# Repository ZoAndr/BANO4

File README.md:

# BANO4
OnBoard Aviation Navigation Lights

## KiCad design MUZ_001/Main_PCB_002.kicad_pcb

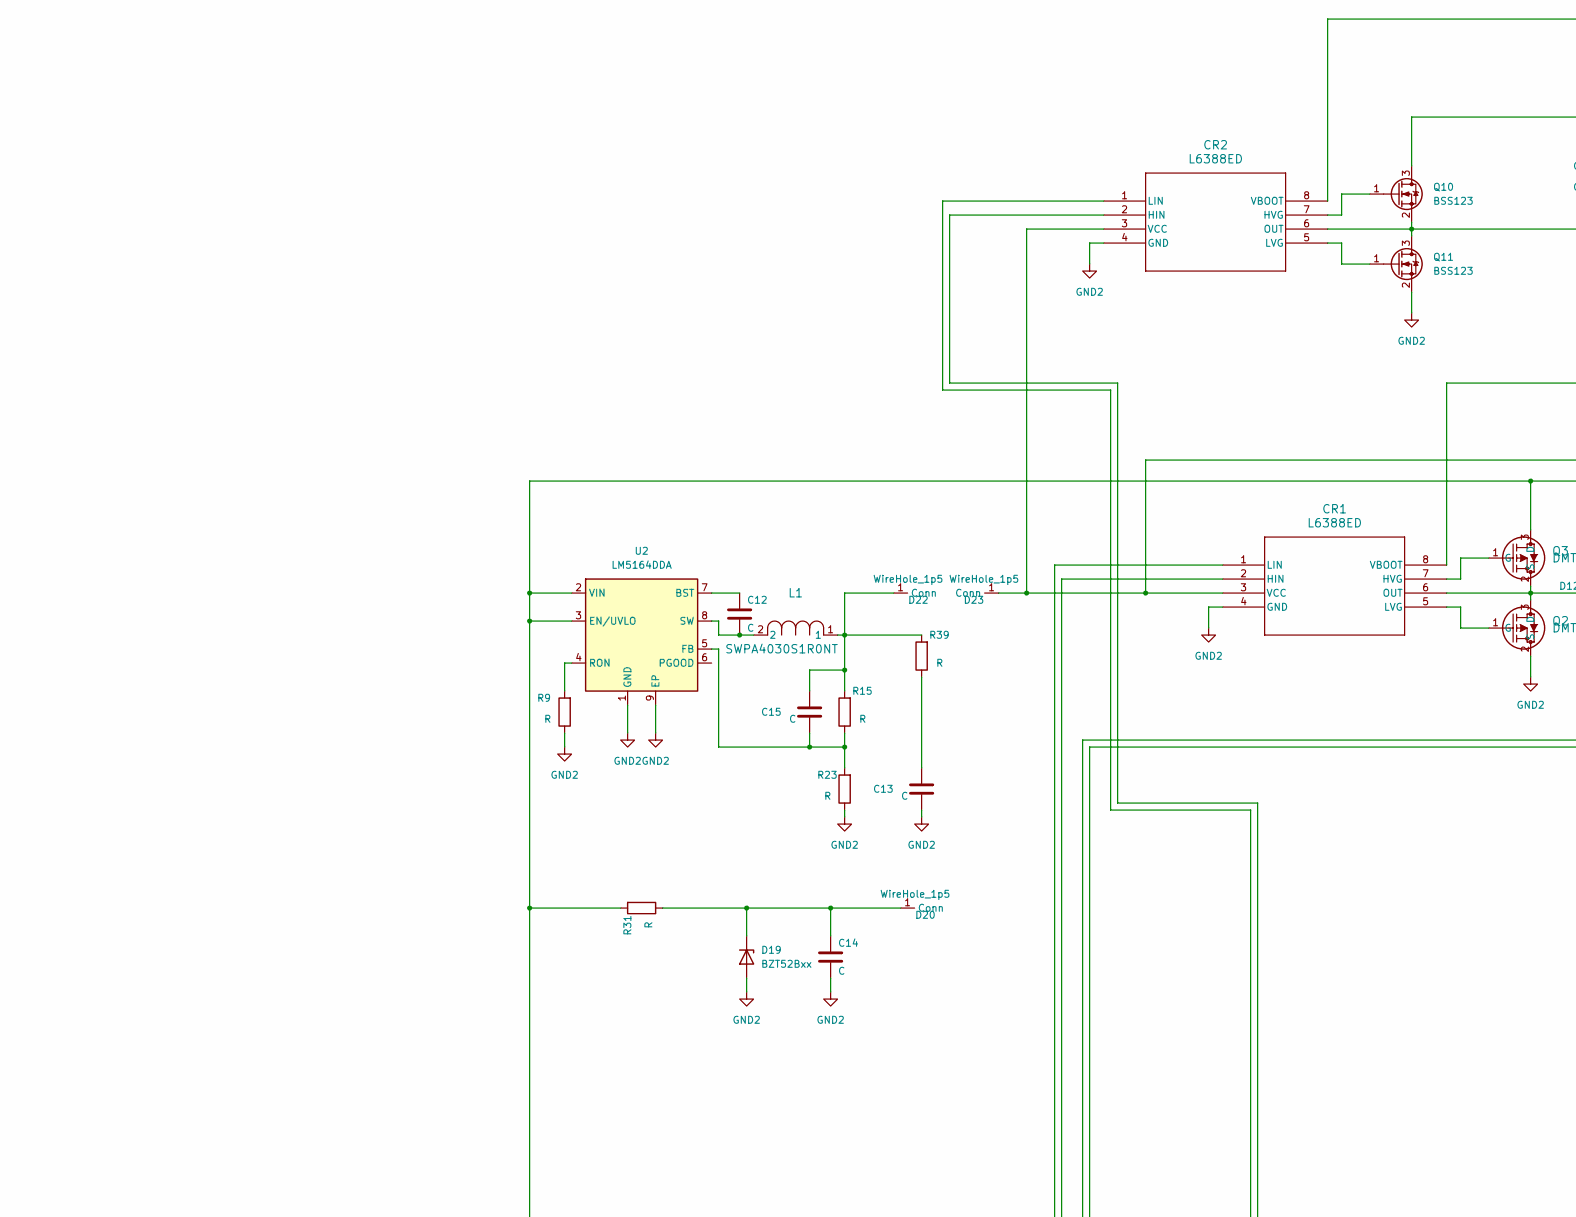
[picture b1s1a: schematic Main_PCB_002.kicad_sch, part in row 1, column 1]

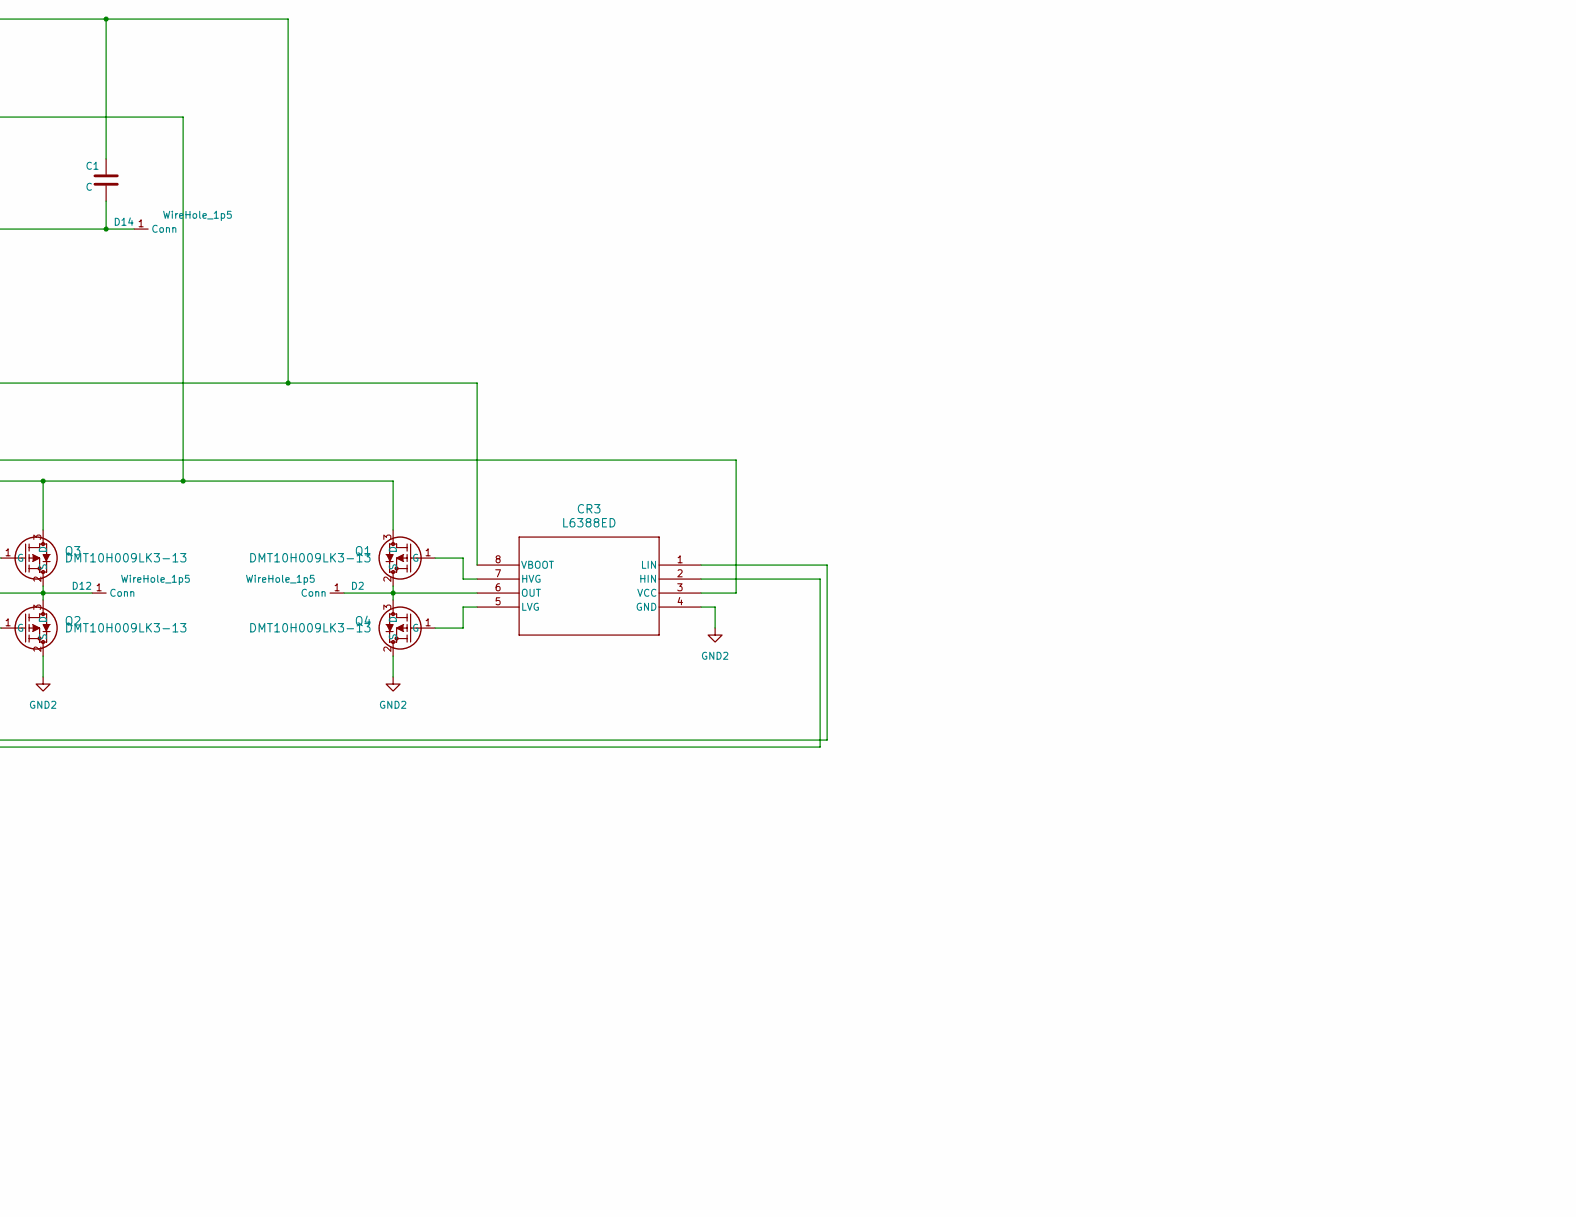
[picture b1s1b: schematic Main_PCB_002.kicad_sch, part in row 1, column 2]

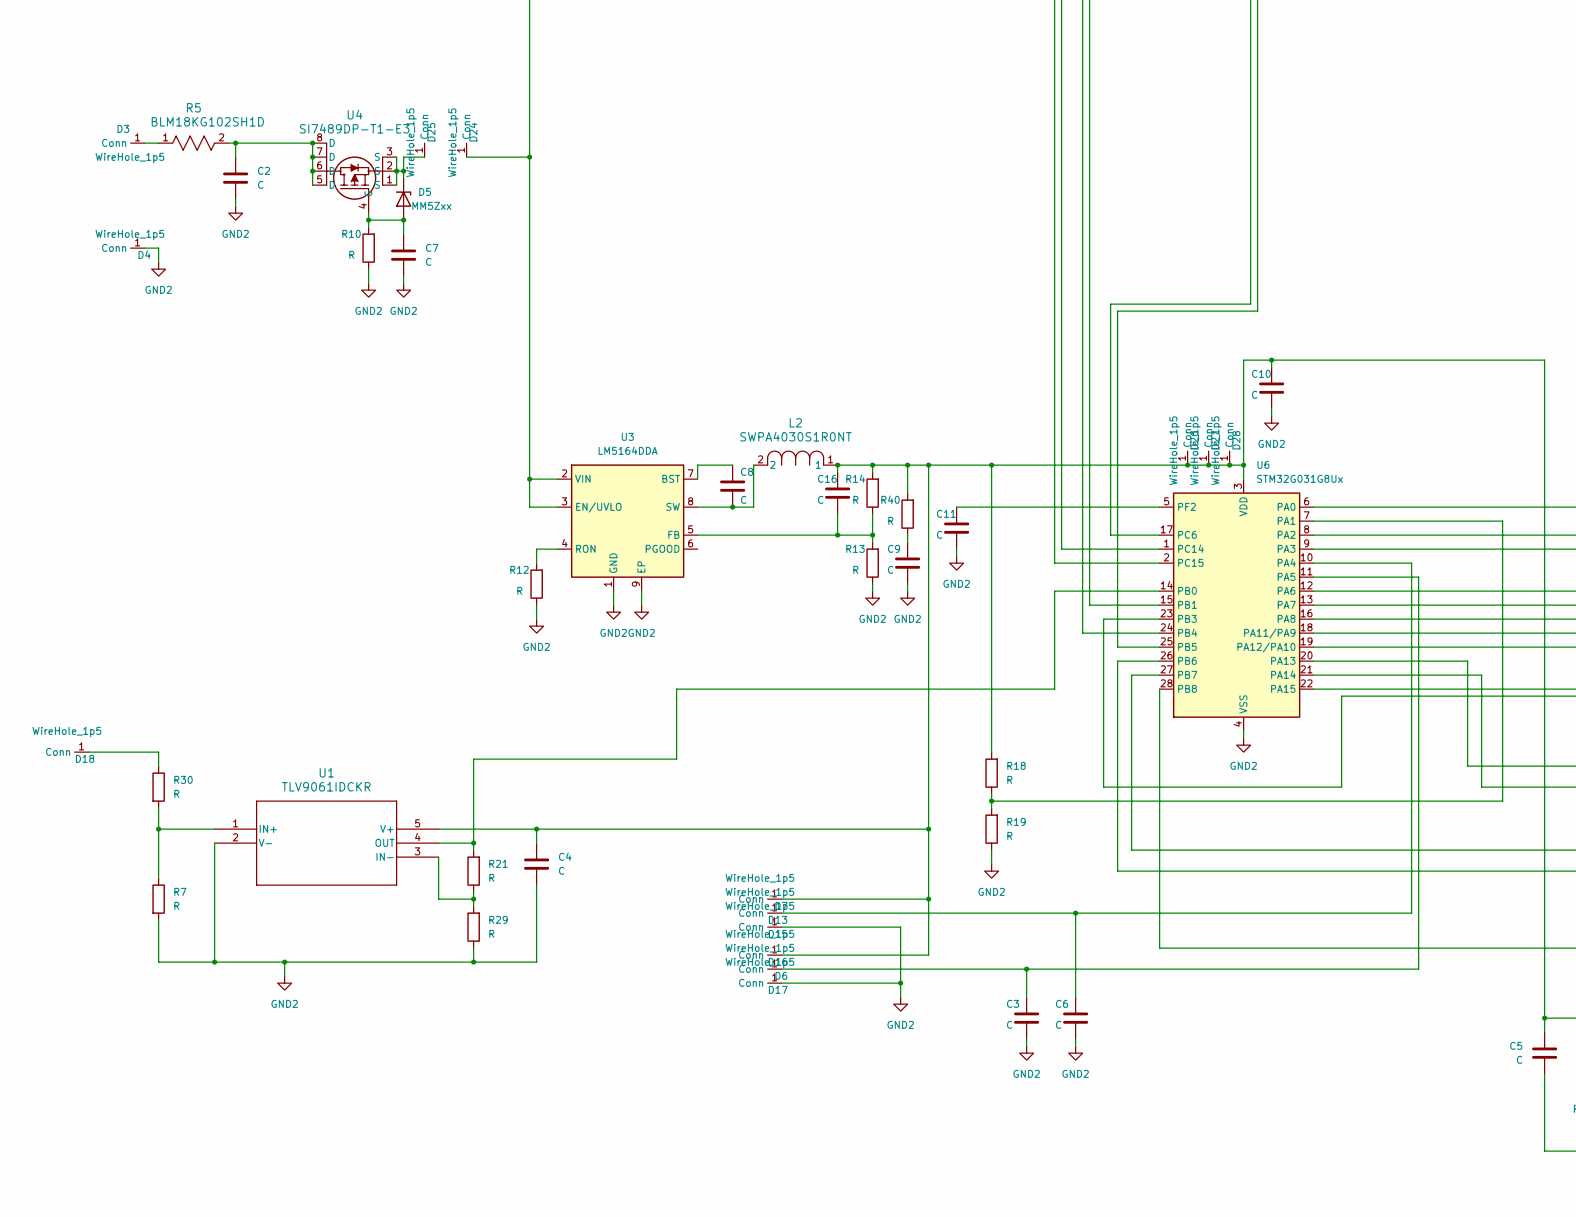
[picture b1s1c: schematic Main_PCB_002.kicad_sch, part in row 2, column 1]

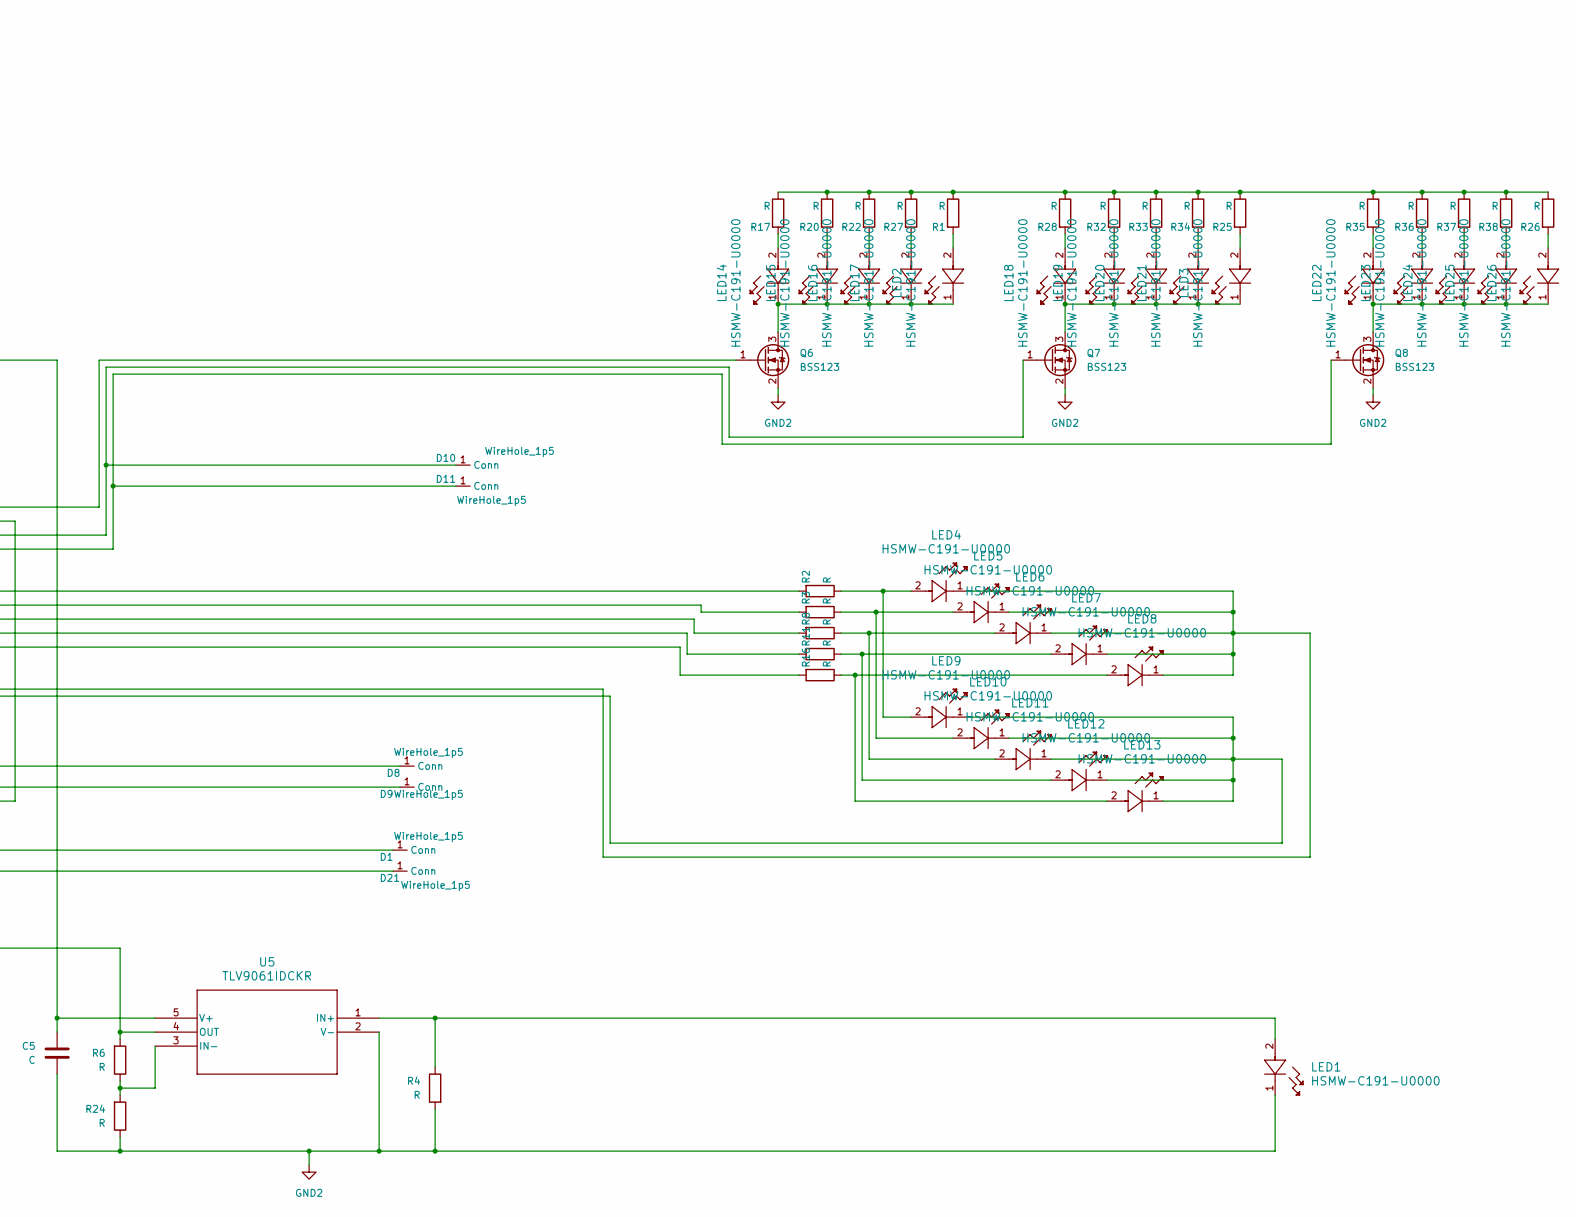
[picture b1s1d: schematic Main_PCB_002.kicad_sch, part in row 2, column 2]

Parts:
C1, C3, C6, C9, C13: C; C_0805_2012Metric
C2: C; C_0805_2012Metric_Pad1.18x1.45mm_HandSolder
C4, C5, C7, C16: C; C_0402_1005Metric_Pad0.74x0.62mm_HandSolder
C8, C10, C11, C12, C14: C; C_0603_1608Metric_Pad1.08x0.95mm_HandSolder
C15: C; C_0402_1005Metric
CR1, CR2, CR3: L6388ED; SO-8_STM
D1, D2, D3, D4, D6, D7, D8, D9, D10, D11, D12, D13, D14, D15, D16, D17, D18, D20, D21, D22, D23, D24, D25, D26, D27, D28: WireHole_1p5; WireHole_1p2
D5: MM5Zxx; D_SOD-523
D19: BZT52Bxx; D_SOD-123F
L1, L2: SWPA4030S1R0NT; IND_VLS252012_TDK
LED1, LED2, LED3, LED4, LED5, LED6, LED7, LED8, LED9, LED10, LED11, LED12, LED13, LED14, LED15, LED16, LED17, LED18, LED19, LED20, LED21, LED22, LED23, LED24, LED25, LED26: HSMW-C191-U0000; LED_91-U0000
Q1, Q2, Q3, Q4: DMT10H009LK3-13; QPMOS1G2S3D_TO252_DIO
Q6, Q7, Q8, Q10, Q11: BSS123; SOT-23
R1, R2, R3, R4, R6, R7, R8, R9, R10, R11, R12, R13, R14, R15, R16, R17, R18, R19, R20, R21, R22, R23, R24, R25, R26, R27, R28, R29, R30, R31, R32, R33, R34, R35, R36, R37, R38, R39, R40: R; R_0402_1005Metric_Pad0.72x0.64mm_HandSolder
R5: BLM18KG102SH1D; RES_0603_1P6XP8_MUR
U1, U5: TLV9061IDCKR; DCK5_TEX
U2, U3: LM5164DDA; HSOP-8-1EP_3.9x4.9mm_P1.27mm_EP2.41x3.1mm_ThermalVias
U4: SI7489DP-T1-E3; POWERPAK_SO-8_SINGLE_VIS
U6: STM32G031G8Ux; QFN-28_4x4mm_P0.5mm

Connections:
GND2: C2.2, C3.2, C4.2, C5.2, C6.2, C7.2, C9.2, C10.2, C11.2, C13.2, C14.2, CR1.4 (GND), CR2.4 (GND), CR3.4 (GND), D4.1 (Conn), D15.1 (Conn), D17.1 (Conn), D19.2 (A), LED1.1, Q2.2 (S), Q4.2 (S), Q6.2 (S), Q7.2 (S), Q8.2 (S), Q11.2 (S), R4.2, R7.2, R9.1, R10.1, R12.1, R13.1, R19.1, R23.1, R24.1, R29.1, U1.2 (V-), U2.1 (GND), U2.9 (EP), U3.1 (GND), U3.9 (EP), U5.2 (V-), U6.4 (VSS)
unnamed: C2.1, R5.2, U4.5 (D), U4.6 (D), U4.7 (D), U4.8 (D)
unnamed: C9.1, R40.1
unnamed: C13.1, R39.1
unnamed: CR1.2 (HIN), U6.1 (PC14)
unnamed: CR1.7 (HVG), Q3.1 (G)
unnamed: CR1.1 (LIN), U6.2 (PC15)
unnamed: CR1.5 (LVG), Q2.1 (G)
unnamed: CR1.6 (OUT), D12.1 (Conn), Q2.3 (D), Q3.2 (S)
unnamed: C1.1, CR1.8 (VBOOT), CR2.8 (VBOOT), CR3.8 (VBOOT)
unnamed: CR1.3 (VCC), CR2.3 (VCC), CR3.3 (VCC), D23.1 (Conn)
unnamed: CR2.2 (HIN), U6.25 (PB5)
unnamed: CR2.7 (HVG), Q10.1 (G)
unnamed: CR2.1 (LIN), U6.17 (PC6)
unnamed: CR2.5 (LVG), Q11.1 (G)
unnamed: C1.2, CR2.6 (OUT), D14.1 (Conn), Q10.2 (S), Q11.3 (D)
unnamed: CR3.2 (HIN), U6.15 (PB1)
unnamed: CR3.7 (HVG), Q1.1 (G)
unnamed: CR3.1 (LIN), U6.24 (PB4)
unnamed: CR3.5 (LVG), Q4.1 (G)
unnamed: CR3.6 (OUT), D2.1 (Conn), Q1.2 (S), Q4.3 (D)
unnamed: D1.1 (Conn), U6.27 (PB7)
unnamed: D3.1 (Conn), R5.1
unnamed: C7.1, D5.2 (A), R10.2, U4.4 (G)
unnamed: C3.1, D6.1 (Conn), U6.11 (PA5)
unnamed: D8.1 (Conn), U6.20 (PA13)
unnamed: D9.1 (Conn), U6.21 (PA14)
unnamed: D10.1 (Conn), Q7.1 (G), U6.8 (PA2)
unnamed: D11.1 (Conn), Q8.1 (G), U6.9 (PA3)
unnamed: C6.1, D13.1 (Conn), U6.10 (PA4)
unnamed: C4.1, C5.1, C10.1, C16.1, D7.1 (Conn), D16.1 (Conn), D26.1 (Conn), D27.1 (Conn), D28.1 (Conn), L2.1, R14.2, R18.2, R40.2, U1.5 (V+), U5.5 (V+), U6.3 (VDD)
unnamed: D18.1 (Conn), R30.1
unnamed: C14.1, D19.1 (K), D20.1 (Conn), R31.1
unnamed: D21.1 (Conn), U6.26 (PB6)
unnamed: C15.1, D22.1 (Conn), L1.1, R15.2, R39.2
unnamed: D24.1 (Conn), Q1.3 (D), Q3.3 (D), Q10.3 (D), R31.2, U2.2 (VIN), U2.3 (EN/UVLO), U3.2 (VIN), U3.3 (EN/UVLO)
unnamed: D5.1 (K), D25.1 (Conn), U4.1 (S), U4.2 (S), U4.3 (S)
unnamed: LED2.2, R1.2
unnamed: LED3.2, R25.2
unnamed: LED4.2, LED9.2, R2.1
unnamed: LED5.2, LED10.2, R3.1
unnamed: LED6.2, LED11.2, R8.1
unnamed: LED7.2, LED12.2, R11.1
unnamed: LED8.2, LED13.2, R16.1
unnamed: LED14.2, R17.2
unnamed: LED15.2, R20.2
unnamed: LED16.2, R22.2
unnamed: LED17.2, R27.2
unnamed: LED18.2, R28.2
unnamed: LED19.2, R32.2
unnamed: LED20.2, R33.2
unnamed: LED21.2, R34.2
unnamed: LED22.2, R35.2
unnamed: LED23.2, R36.2
unnamed: LED24.2, R37.2
unnamed: LED25.2, R38.2
unnamed: LED26.2, R26.2
unnamed: LED2.1, LED14.1, LED15.1, LED16.1, LED17.1, Q6.3 (D)
unnamed: Q6.1 (G), U6.6 (PA0)
unnamed: LED3.1, LED18.1, LED19.1, LED20.1, LED21.1, Q7.3 (D)
unnamed: LED22.1, LED23.1, LED24.1, LED25.1, LED26.1, Q8.3 (D)
unnamed: R1.1, R17.1, R20.1, R22.1, R25.1, R26.1, R27.1, R28.1, R32.1, R33.1, R34.1, R35.1, R36.1, R37.1, R38.1
unnamed: R7.1, R30.2, U1.1 (IN+)
unnamed: R21.1, R29.2, U1.3 (IN-)
unnamed: R21.2, U1.4 (OUT), U6.14 (PB0)
unnamed: C12.1, U2.7 (BST)
unnamed: C15.2, R15.1, R23.2, U2.5 (FB)
unnamed: R9.2, U2.4 (RON)
unnamed: C12.2, L1.2, U2.8 (SW)
unnamed: C8.1, U3.7 (BST)
unnamed: C16.2, R13.2, R14.1, U3.5 (FB)
unnamed: R12.2, U3.4 (RON)
unnamed: C8.2, L2.2, U3.8 (SW)
unnamed: LED1.2, R4.1, U5.1 (IN+)
unnamed: R6.1, R24.2, U5.3 (IN-)
unnamed: R6.2, U5.4 (OUT), U6.28 (PB8)
unnamed: R18.1, R19.2, U6.7 (PA1)
unnamed: R2.2, U6.12 (PA6)
unnamed: R3.2, U6.13 (PA7)
unnamed: R8.2, U6.16 (PA8)
unnamed: R11.2, U6.18 (PA11/PA9)
unnamed: R16.2, U6.19 (PA12/PA10)
unnamed: LED4.1, LED5.1, LED6.1, LED7.1, LED8.1, U6.22 (PA15)
unnamed: LED9.1, LED10.1, LED11.1, LED12.1, LED13.1, U6.23 (PB3)
unnamed: C11.1, U6.5 (PF2)

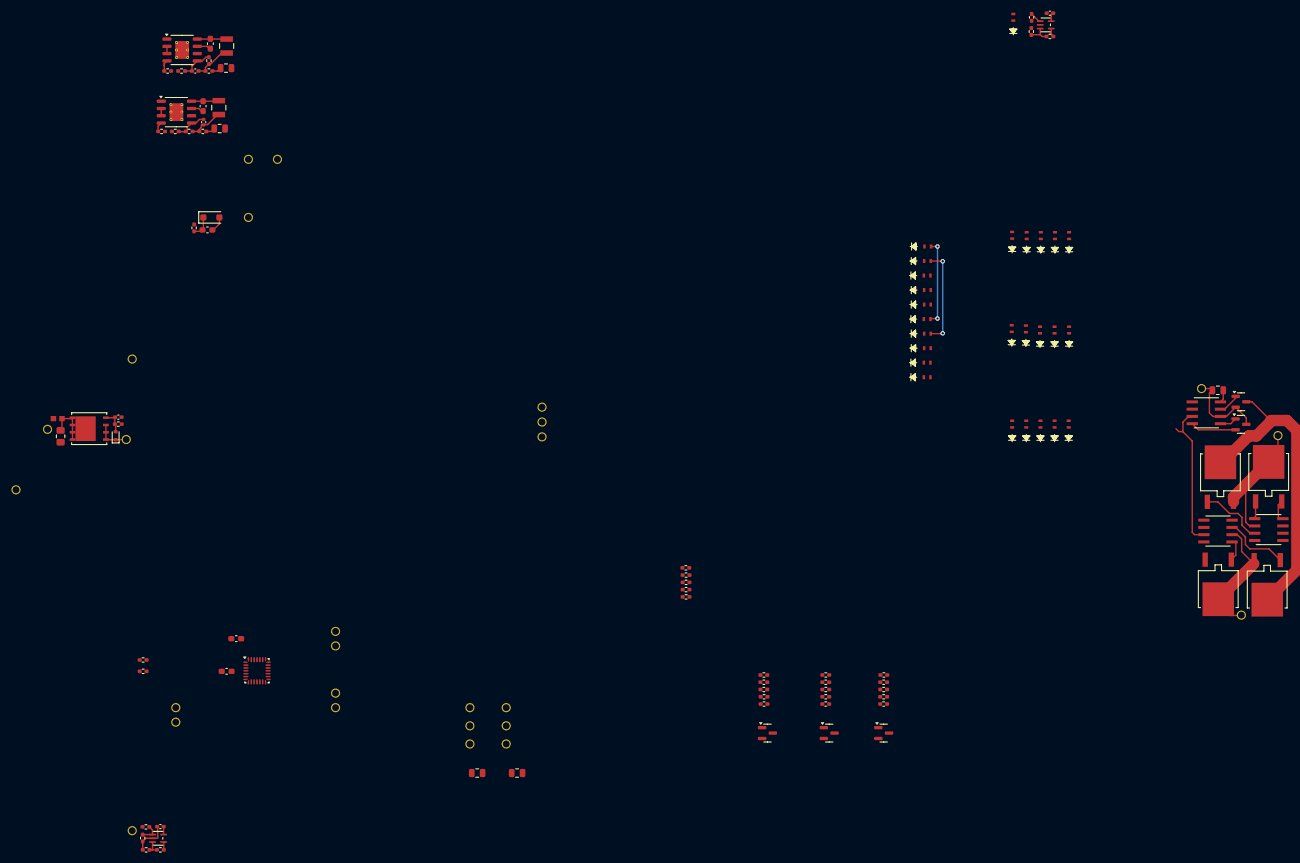
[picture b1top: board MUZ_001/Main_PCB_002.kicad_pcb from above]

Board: 2 copper layers, 130 parts (0 on the bottom side), 85 nets.

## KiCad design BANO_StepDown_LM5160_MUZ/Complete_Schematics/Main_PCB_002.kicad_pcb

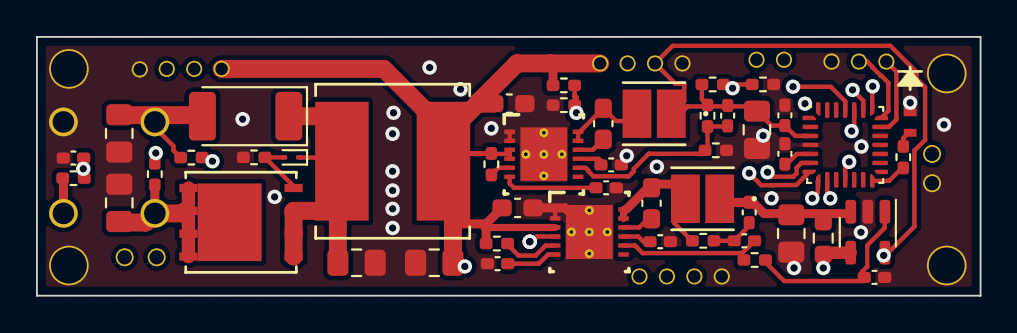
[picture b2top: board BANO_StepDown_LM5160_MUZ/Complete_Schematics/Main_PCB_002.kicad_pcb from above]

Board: 4 copper layers, 52.4 x 14.4 mm, 77 parts (0 on the bottom side), 39 nets.

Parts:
C1, C2, C4, C5, C15, C19: C; C_0805_2012Metric_Pad1.18x1.45mm_HandSolder
C3, C6, C7, C9, C11, C13, C16, C17, C18, C20, C21: C; C_0402_1005Metric_Pad0.74x0.62mm_HandSolder
C8, C10, C12, C14: C; C_0603_1608Metric_Pad1.08x0.95mm_HandSolder
D1, D2, D3, D19: WireHole_1p5; WireHole_1p2
D4: 1N5711UR; D_MELF
D5: MM5Zxx; D_SOD-923
D6, D7, D8, D9, D10, D11, D12, D13, D14, D20, D21, D22, D23, D24, D25, D26, D27: WireHole_1p5; WireHole_0p7
D15, D16, D17, D18: WireHole_1p5; WireHole_0p8
D28, D29, D30, D31: WireHole_1p5; WireHole_2p0
L1: SWPA8040S220MT; IND_SWPA8040S_SNL
L2, L3: SWPA3015S4R7MT; IND_SWPA3015S_SNL
LED1: HSMW-C191-U0000; LED_91-U0000
R1, R2, R3, R4, R5, R6, R7, R8, R9, R10, R11, R12, R13, R14, R15: R; R_0402_1005Metric_Pad0.72x0.64mm_HandSolder
R16: R; R_0603_1608Metric_Pad0.98x0.95mm_HandSolder
U1: SI7489DP-T1-E3; POWERPAK_SO-8_SINGLE_VIS
U2: STM32G031G8Ux; QFN-28_4x4mm_P0.5mm
U3, U4: LM5160ADNTR; DNT0012B
U5: INA193; SOT-23-5

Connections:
GND2: C1.2, C2.2, C3.2, C4.2, C5.2, C6.2, C7.2, C8.2, C9.2, C10.2, C11.2, C13.2, C15.2, C16.2, C19.2, C20.2, D10.1 (Conn), D14.1 (Conn), D18.1 (Conn), D19.1 (Conn), D20.1 (Conn), D21.1 (Conn), D28.1 (Conn), D29.1 (Conn), D30.1 (Conn), D31.1 (Conn), LED1.1, R4.1, R6.1, R8.1, R15.1, U2.4 (VSS), U3.1 (AGND), U3.2 (PGND), U3.13 (PAD), U3.V, U4.1 (AGND), U4.2 (PGND), U4.13 (PAD), U4.V, U5.2 (GND)
unnamed: C12.2, L2.2, R12.2, U3.11 (SW), U3.12 (SW)
unnamed: C14.2, L3.2, U4.11 (SW), U4.12 (SW)
unnamed: C17.2, C18.1, R12.1
unnamed: D1.1 (Conn), R3.2
unnamed: C1.1, D2.1 (Conn), D4.2 (A), R2.1
unnamed: C2.1, D3.1 (Conn), R1.1, U1.5 (D), U1.6 (D), U1.7 (D), U1.8 (D)
unnamed: C4.1, D4.1 (K), D5.1 (K), L1.2, U1.1 (S), U1.2 (S), U1.3 (S)
unnamed: D5.2 (A), R4.2, U1.4 (G)
unnamed: D6.1 (Conn), U2.8 (PA2)
unnamed: D7.1 (Conn), U2.9 (PA3)
unnamed: D8.1 (Conn), U2.20 (PA13)
unnamed: D9.1 (Conn), U2.21 (PA14)
unnamed: C5.1, C8.1, C10.1, D11.1 (Conn), D26.1 (Conn), D27.1 (Conn), L1.1, R7.2, R10.2, R11.2, U3.3 (VIN), U4.3 (VIN), U4.4 (EN_UVLO)
unnamed: D12.1 (Conn), D24.1 (Conn), D25.1 (Conn), U2.22 (PA15)
unnamed: C7.1, C19.1, C20.1, C21.1, D13.1 (Conn), D22.1 (Conn), D23.1 (Conn), L3.1, R5.2, R14.2, U2.3 (VDD), U5.5 (V+)
unnamed: D15.1 (Conn), R16.1, U5.4 (-)
unnamed: D16.1 (Conn), D17.1 (Conn)
unnamed: LED1.2, R9.1
unnamed: R13.1, U5.1
unnamed: R7.1, R8.2, U2.6 (PA0)
unnamed: R5.1, R6.2, U2.7 (PA1)
unnamed: C3.1, R3.1, U2.11 (PA5)
unnamed: R9.2, U2.14 (PB0)
unnamed: U2.23 (PB3), U3.4 (EN_UVLO)
unnamed: R2.2, U2.24 (PB4)
unnamed: R1.2, U2.25 (PB5)
unnamed: C6.1, U2.5 (PF2)
unnamed: C12.1, U3.10 (BST)
unnamed: C18.2, R13.2, U3.8 (FB)
unnamed: R10.1, U3.5 (RON)
unnamed: C9.1, U3.6 (SS)
unnamed: C13.1, U3.9 (VCC)
unnamed: C14.1, U4.10 (BST)
unnamed: C21.2, R14.1, R15.2, U4.8 (FB)
unnamed: R11.1, U4.5 (RON)
unnamed: C11.1, U4.6 (SS)
unnamed: C16.1, U4.9 (VCC)
unnamed: C15.1, C17.1, L2.1, R16.2, U5.3 (+)

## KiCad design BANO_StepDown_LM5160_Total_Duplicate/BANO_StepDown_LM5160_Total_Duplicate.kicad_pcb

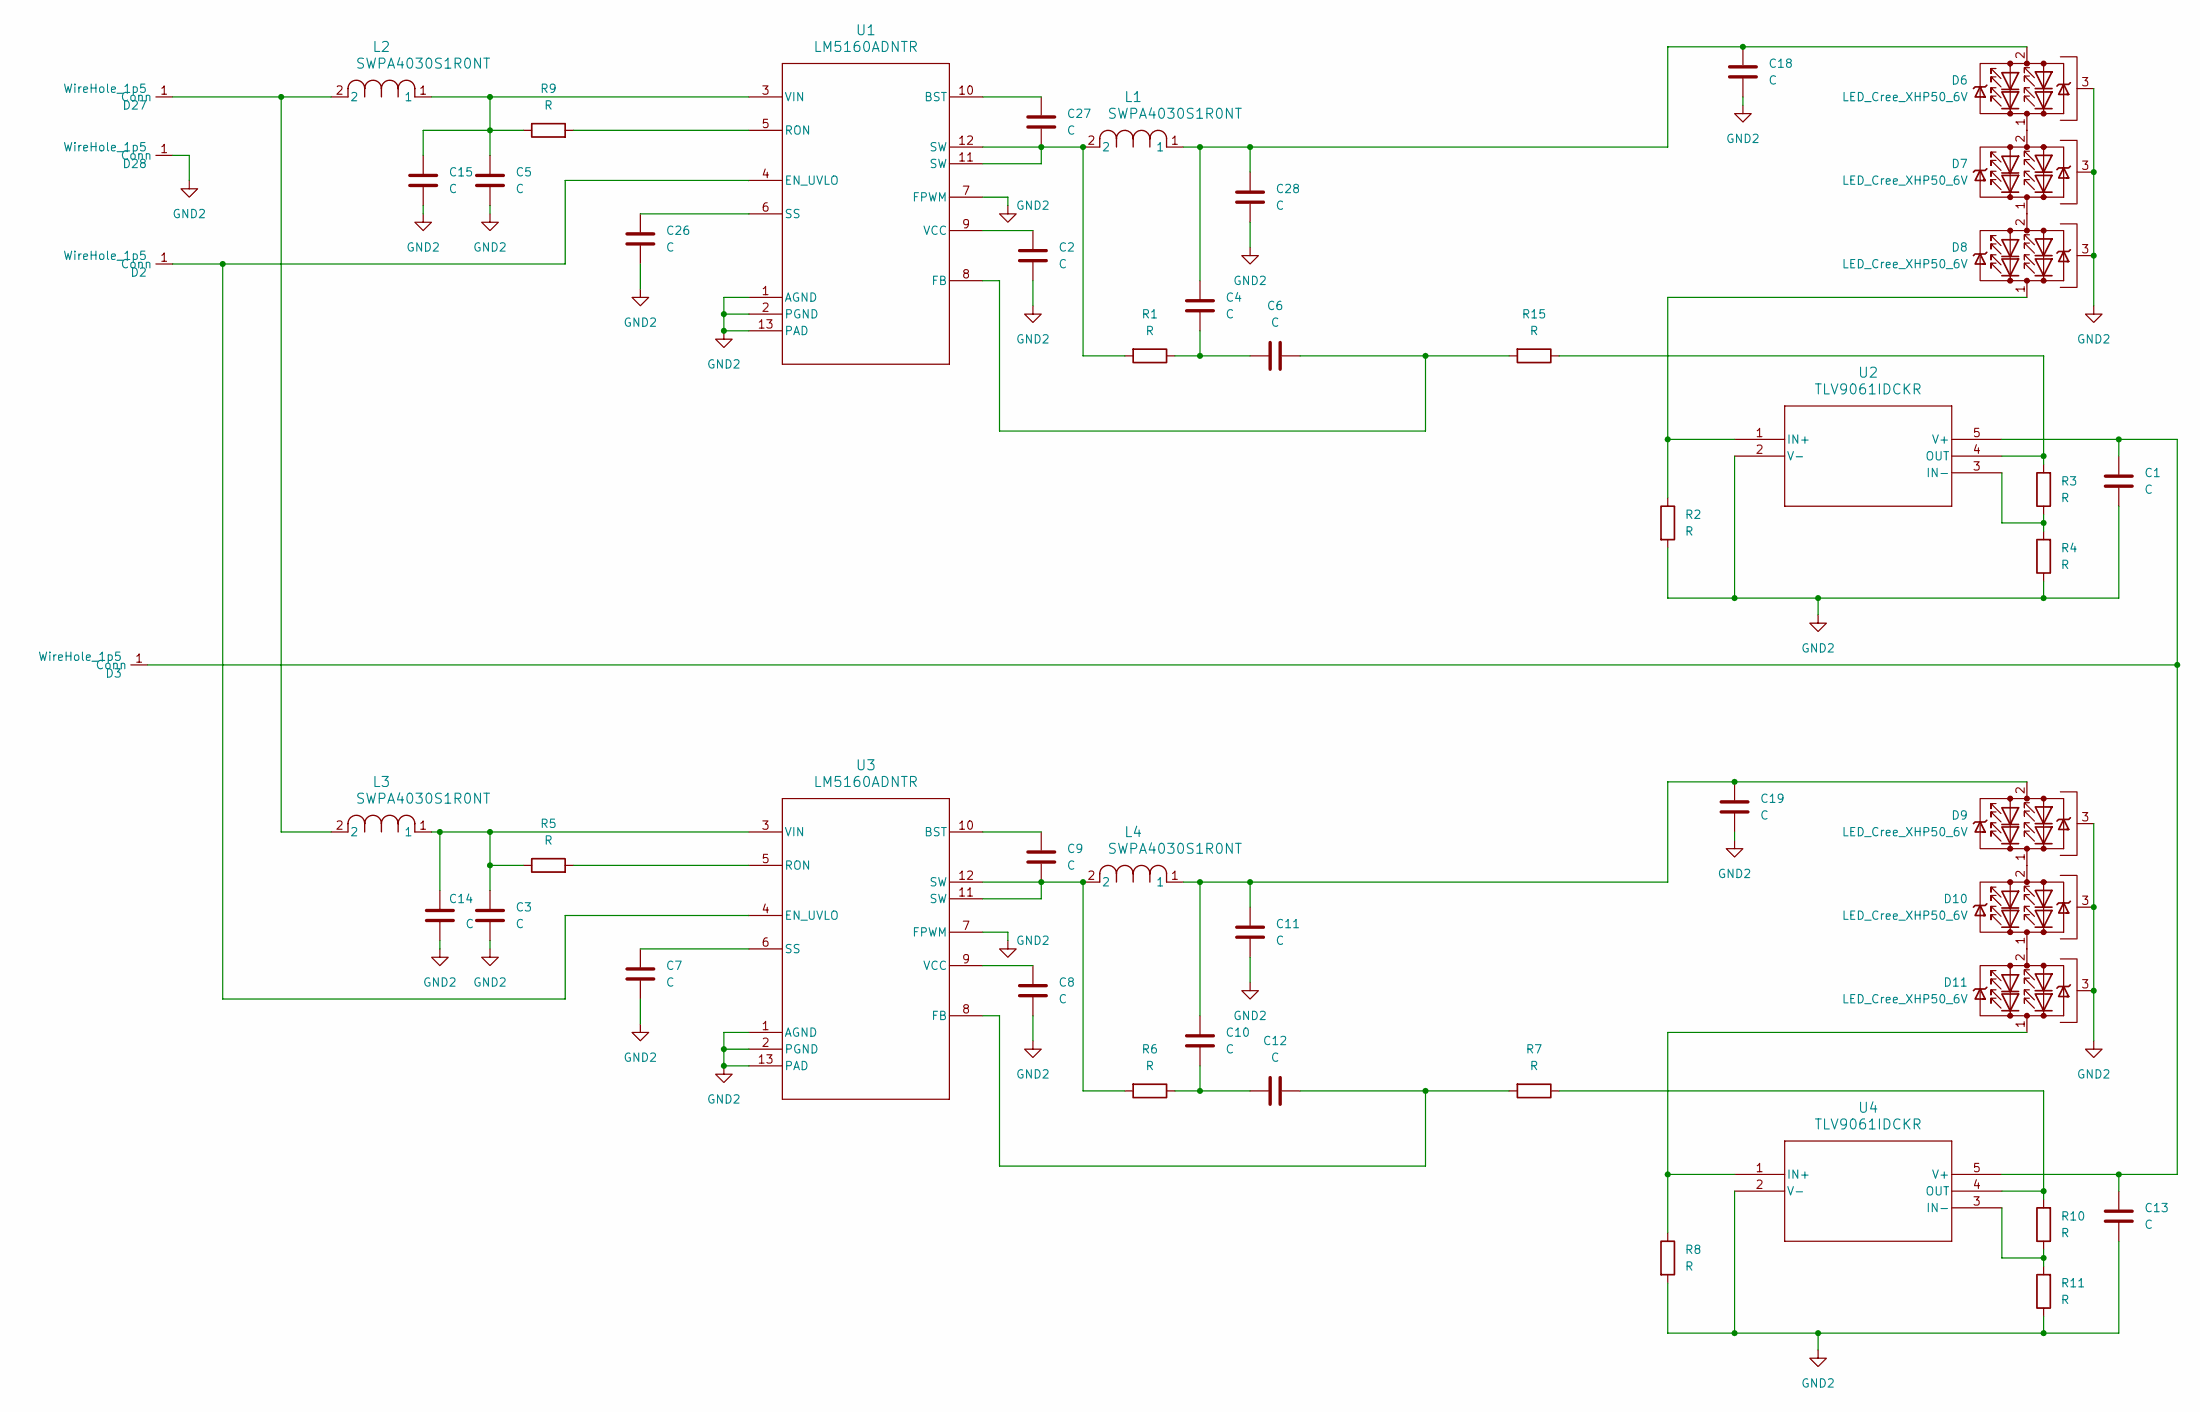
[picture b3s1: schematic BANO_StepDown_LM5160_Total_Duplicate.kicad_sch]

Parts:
C1, C2, C4, C6, C7, C8, C10, C12, C13, C14, C15, C26: C; C_0402_1005Metric_Pad0.74x0.62mm_HandSolder
C3, C5, C18, C19: C; C_0805_2012Metric_Pad1.18x1.45mm_HandSolder
C9, C11, C27, C28: C; C_0603_1608Metric_Pad1.08x0.95mm_HandSolder
D2: WireHole_1p5; Pin_D0.7mm_L6.5mm_W1.8mm_FlatFork
D3, D27, D28: WireHole_1p5; WireHole_1p2
D6, D7, D8, D9, D10, D11: LED_Cree_XHP50_6V; LED_Cree-XHP50_6V
L1, L2, L3, L4: SWPA4030S1R0NT; IND_SWPA4030S_SNL
R1, R3, R4, R6, R7, R10, R11, R15: R; R_0402_1005Metric_Pad0.72x0.64mm_HandSolder
R2, R5, R8, R9: R; R_0603_1608Metric_Pad0.98x0.95mm_HandSolder
U1, U3: LM5160ADNTR; DNT0012B
U2, U4: TLV9061IDCKR; DCK5_TEX

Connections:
GND2: C1.2, C2.2, C3.2, C5.2, C7.2, C8.2, C11.2, C13.2, C14.2, C15.2, C18.2, C19.2, C26.2, C28.2, D6.3 (PAD), D7.3 (PAD), D8.3 (PAD), D9.3 (PAD), D10.3 (PAD), D11.3 (PAD), D28.1 (Conn), R2.2, R4.1, R8.2, R11.1, U1.1 (AGND), U1.2 (PGND), U1.7 (FPWM), U1.13 (PAD), U1.V, U2.2 (V-), U3.1 (AGND), U3.2 (PGND), U3.7 (FPWM), U3.13 (PAD), U3.V, U4.2 (V-)
unnamed: C4.2, C6.1, R1.1
unnamed: C9.2, L4.2, R6.2, U3.11 (SW), U3.12 (SW)
unnamed: C10.2, C12.1, R6.1
unnamed: C27.2, L1.2, R1.2, U1.11 (SW), U1.12 (SW)
unnamed: D2.1, U1.4 (EN_UVLO), U3.4 (EN_UVLO)
unnamed: C1.1, C13.1, D3.1 (Conn), U2.5 (V+), U4.5 (V+)
unnamed: C4.1, C18.1, C28.1, D6.2 (A), L1.1
unnamed: D6.1 (K), D7.2 (A)
unnamed: D7.1 (K), D8.2 (A)
unnamed: D8.1 (K), R2.1, U2.1 (IN+)
unnamed: C10.1, C11.1, C19.1, D9.2 (A), L4.1
unnamed: D9.1 (K), D10.2 (A)
unnamed: D10.1 (K), D11.2 (A)
unnamed: D11.1 (K), R8.1, U4.1 (IN+)
unnamed: D27.1 (Conn), L2.2, L3.2
unnamed: C27.1, U1.10 (BST)
unnamed: C6.2, R15.2, U1.8 (FB)
unnamed: R9.2, U1.5 (RON)
unnamed: C26.1, U1.6 (SS)
unnamed: C2.1, U1.9 (VCC)
unnamed: C5.1, C15.1, L2.1, R9.1, U1.3 (VIN)
unnamed: R3.1, R4.2, U2.3 (IN-)
unnamed: R3.2, R15.1, U2.4 (OUT)
unnamed: C9.1, U3.10 (BST)
unnamed: C12.2, R7.2, U3.8 (FB)
unnamed: R5.2, U3.5 (RON)
unnamed: C7.1, U3.6 (SS)
unnamed: C8.1, U3.9 (VCC)
unnamed: C3.1, C14.1, L3.1, R5.1, U3.3 (VIN)
unnamed: R10.1, R11.2, U4.3 (IN-)
unnamed: R7.1, R10.2, U4.4 (OUT)

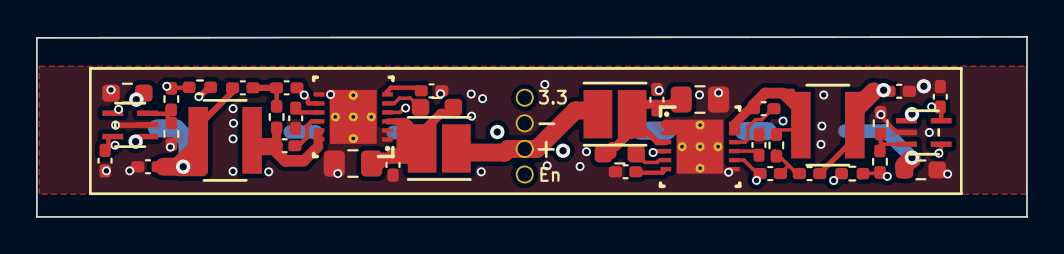
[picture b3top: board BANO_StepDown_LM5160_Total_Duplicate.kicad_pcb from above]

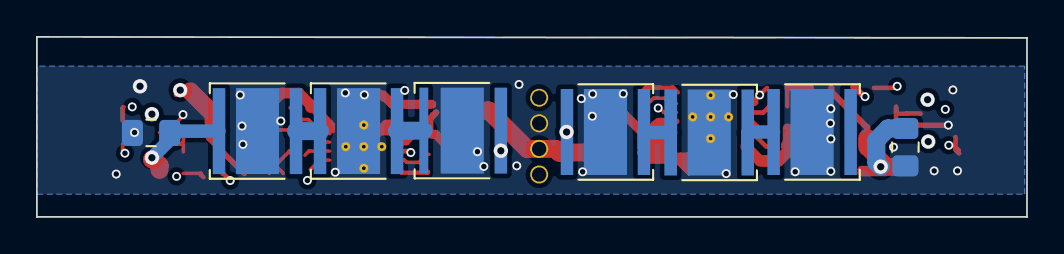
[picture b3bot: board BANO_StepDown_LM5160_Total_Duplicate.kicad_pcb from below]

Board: 4 copper layers, 55.0 x 10.0 mm, 49 parts (8 on the bottom side), 32 nets.

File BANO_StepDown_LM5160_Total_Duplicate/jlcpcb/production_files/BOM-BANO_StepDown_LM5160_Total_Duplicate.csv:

Comment,Designator,Footprint,LCSC
C,"C11,C28",C_0402_1005Metric_Pad0.74x0.62mm_HandSolder,C126632
C,"C12,C6",C_0402_1005Metric_Pad0.74x0.62mm_HandSolder,C1523
C,"C10,C4",C_0402_1005Metric_Pad0.74x0.62mm_HandSolder,C1531
R,"R2,R8",R_0603_1608Metric_Pad0.98x0.95mm_HandSolder,C158894
C,"C26,C7",C_0402_1005Metric_Pad0.74x0.62mm_HandSolder,C16772
R,"R5,R9",R_0603_1608Metric_Pad0.98x0.95mm_HandSolder,C22795
R,"R1,R11,R4,R6",R_0402_1005Metric_Pad0.72x0.64mm_HandSolder,C25744
R,"R10,R3",R_0402_1005Metric_Pad0.72x0.64mm_HandSolder,C25782
R,"R15,R7",R_0402_1005Metric_Pad0.72x0.64mm_HandSolder,C25784
C,"C27,C9",C_0402_1005Metric_Pad0.74x0.62mm_HandSolder,C268018
C,"C2,C8",C_0402_1005Metric_Pad0.74x0.62mm_HandSolder,C29266
C,"C3,C5",C_0805_2012Metric_Pad1.18x1.45mm_HandSolder,C2932476
TLV9061IDCKR,"U2,U4",DCK5_TEX,C398357
LM5160ADNTR,"U1,U3",DNT0012B,C473375
SWPA4030S1R0NT,"L2,L3",IND_SWPA3015S_SNL,C48020
SWPA4030S1R0NT,"L1,L4",IND_SWPA4030S_SNL,C62684
C,"C14,C15",C_0402_1005Metric_Pad0.74x0.62mm_HandSolder,C85858
C,"C1,C13",C_0402_1005Metric_Pad0.74x0.62mm_HandSolder,C88945

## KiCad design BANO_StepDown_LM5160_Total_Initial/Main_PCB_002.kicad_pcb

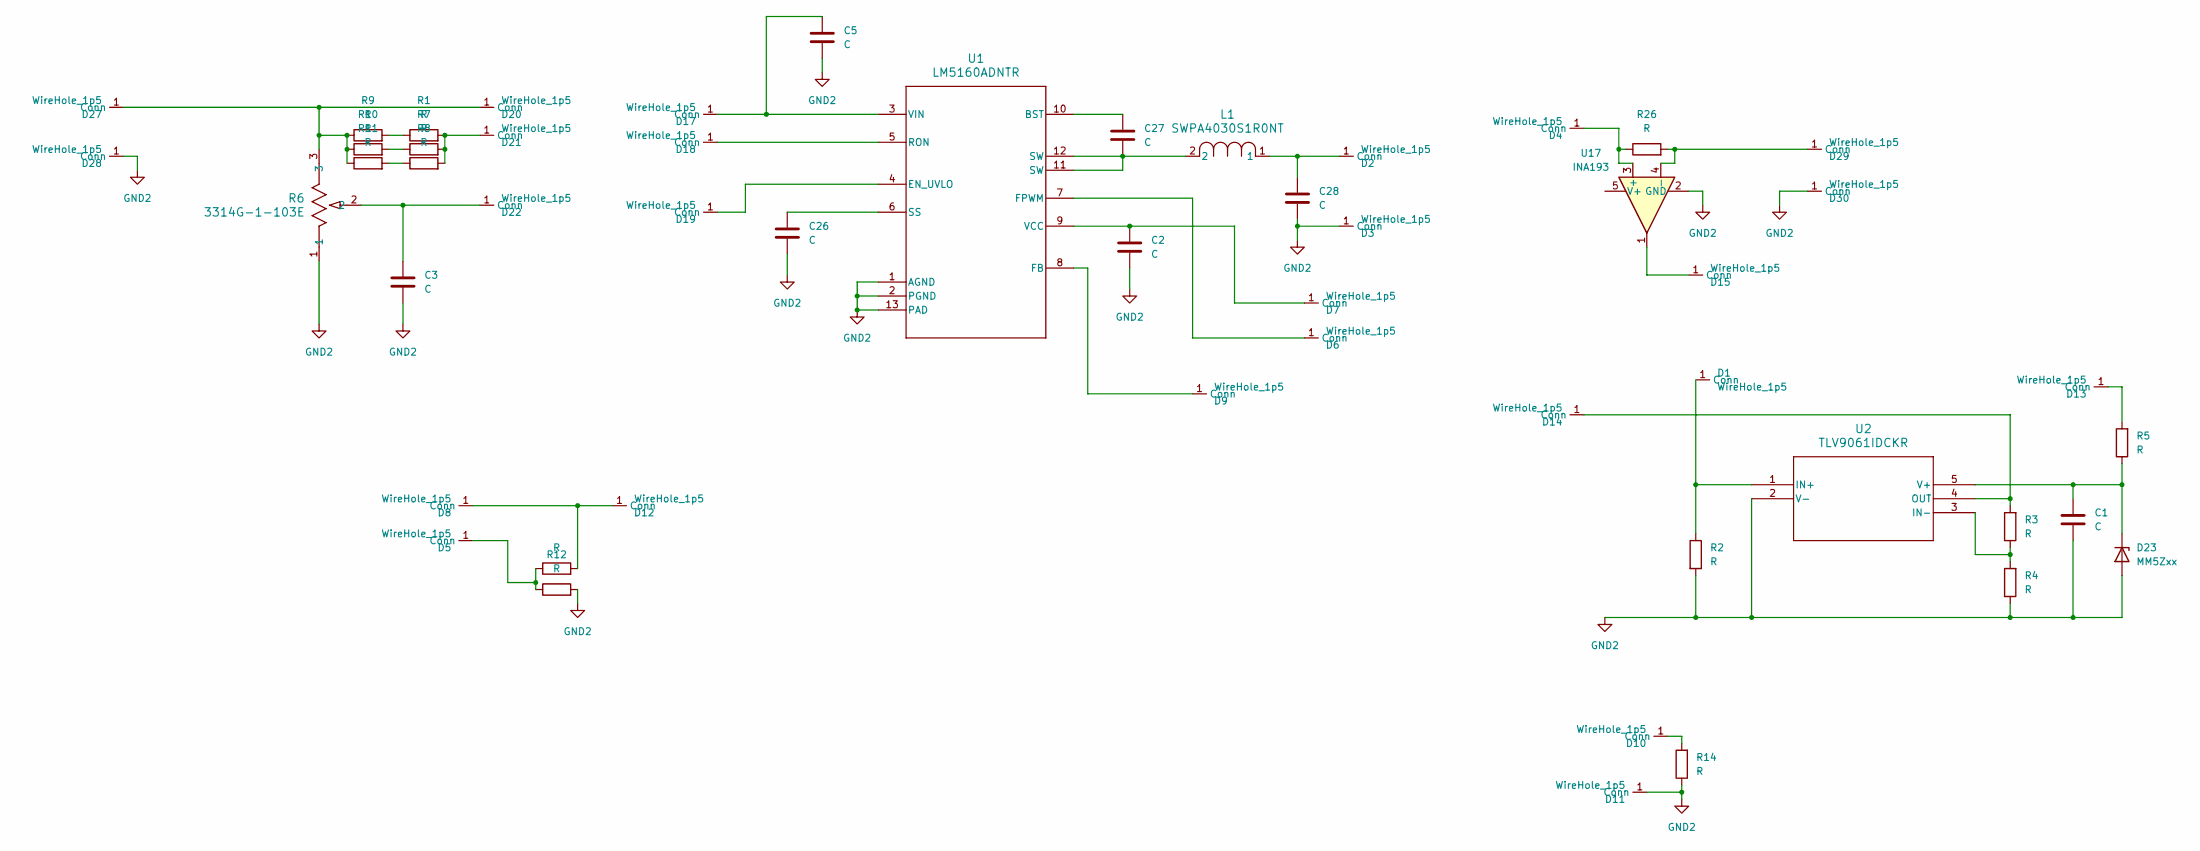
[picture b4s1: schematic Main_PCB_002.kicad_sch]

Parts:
C1, C2, C3, C26, C27: C; C_0603_1608Metric_Pad1.08x0.95mm_HandSolder
C5, C28: C; C_0805_2012Metric_Pad1.18x1.45mm_HandSolder
D1, D2, D3, D4, D5, D6, D7, D8, D9, D10, D11, D12, D13, D14, D15, D17, D18, D19, D20, D21, D22, D27, D28, D29, D30: WireHole_1p5; WireHole_1p2
D23: MM5Zxx; D_SOD-523
L1: SWPA4030S1R0NT; IND_SWPA4030S_SNL
R1, R2, R3, R4, R5, R7, R8, R9, R10, R11, R12, R13, R26: R; R_0603_1608Metric_Pad0.98x0.95mm_HandSolder
R6: 3314G-1-103E; POT_3314G
R14: R; R_2512_6332Metric_Pad1.40x3.35mm_HandSolder
U1: LM5160ADNTR; DNT0012B
U2: TLV9061IDCKR; DCK5_TEX
U17: INA193; SOT-23-5

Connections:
GND2: C1.2, C2.2, C3.2, C5.2, C26.2, C28.2, D3.1 (Conn), D11.1 (Conn), D23.2 (A), D28.1 (Conn), D30.1 (Conn), R2.2, R4.1, R6.1, R12.2, R14.1, U1.1 (AGND), U1.2 (PGND), U1.13 (PAD), U2.2 (V-), U17.2 (GND)
unnamed: C27.2, L1.2, U1.11 (SW), U1.12 (SW)
unnamed: D1.1 (Conn), R2.1, U2.1 (IN+)
unnamed: C28.1, D2.1 (Conn), L1.1
unnamed: D4.1 (Conn), R26.1, U17.3 (+)
unnamed: D5.1 (Conn), R12.1, R13.1
unnamed: D6.1 (Conn), U1.7 (FPWM)
unnamed: C2.1, D7.1 (Conn), U1.9 (VCC)
unnamed: D9.1 (Conn), U1.8 (FB)
unnamed: D10.1 (Conn), R14.2
unnamed: D8.1 (Conn), D12.1 (Conn), R13.2
unnamed: D13.1 (Conn), R5.2
unnamed: D14.1 (Conn), R3.2, U2.4 (OUT)
unnamed: D15.1 (Conn), U17.1
unnamed: C5.1, D17.1 (Conn), U1.3 (VIN)
unnamed: D18.1 (Conn), U1.5 (RON)
unnamed: D19.1 (Conn), U1.4 (EN_UVLO)
unnamed: D20.1 (Conn), D27.1 (Conn), R6.3, R9.1, R10.1, R11.1
unnamed: D21.1 (Conn), R1.2, R7.2, R8.2
unnamed: C3.1, D22.1 (Conn), R6.2
unnamed: C1.1, D23.1 (K), R5.1, U2.5 (V+)
unnamed: D29.1 (Conn), R26.2, U17.4 (-)
unnamed: R1.1, R9.2
unnamed: R7.1, R10.2
unnamed: R8.1, R11.2
unnamed: C27.1, U1.10 (BST)
unnamed: C26.1, U1.6 (SS)
unnamed: R3.1, R4.2, U2.3 (IN-)

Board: 2 copper layers, 52 parts (0 on the bottom side), 28 nets, no tracks yet.
